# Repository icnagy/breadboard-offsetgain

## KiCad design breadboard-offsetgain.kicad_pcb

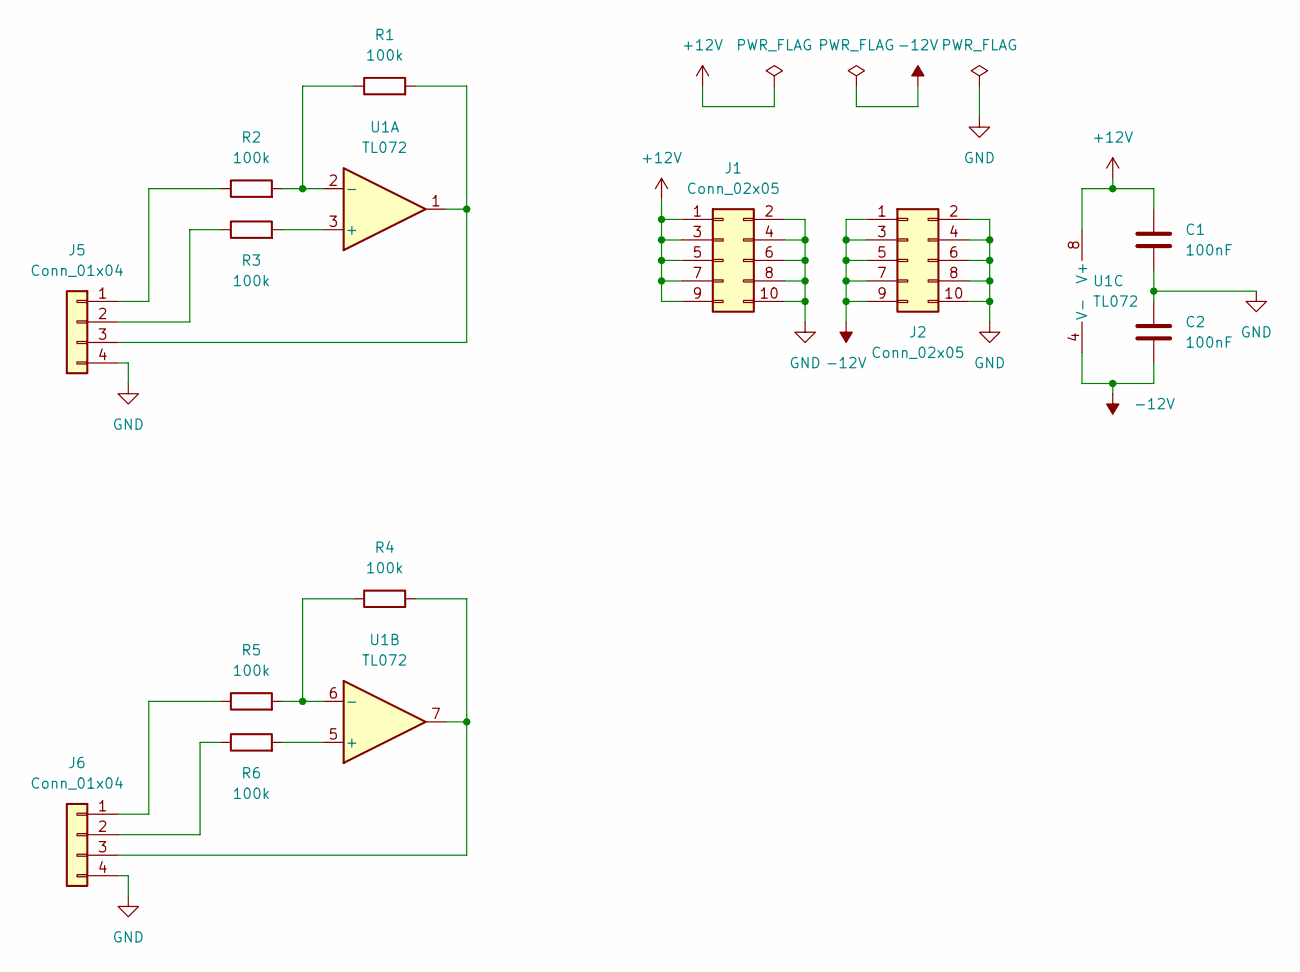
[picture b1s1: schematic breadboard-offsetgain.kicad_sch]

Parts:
C1, C2: 100nF; C_Disc_D4.7mm_W2.5mm_P5.00mm
J1, J2: Conn_02x05; PinHeader_2x05_P2.54mm_Vertical
J5, J6: Conn_01x04; PinHeader_1x04_P2.54mm_Vertical
R1, R2, R3, R4, R5, R6: 100k; R_Axial_DIN0207_L6.3mm_D2.5mm_P2.54mm_Vertical
U1: TL072; DIP-8_W7.62mm_Socket

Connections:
+12V: C1.1, J1.1, J1.3, J1.5, J1.7, J1.9, U1.8 (V+)
-12V: C2.2, J2.1, J2.3, J2.5, J2.7, J2.9, U1.4 (V-)
GND: C1.2, C2.1, J1.2, J1.4, J1.6, J1.8, J1.10, J2.2, J2.4, J2.6, J2.8, J2.10, J5.4, J6.4
unnamed: J5.1, R2.1
unnamed: J5.2, R3.1
unnamed: J5.3, R1.2, U1.1
unnamed: J6.1, R5.1
unnamed: J6.2, R6.1
unnamed: J6.3, R4.2, U1.7
unnamed: R1.1, R2.2, U1.2 (-)
unnamed: R3.2, U1.3 (+)
unnamed: R4.1, R5.2, U1.6 (-)
unnamed: R6.2, U1.5 (+)

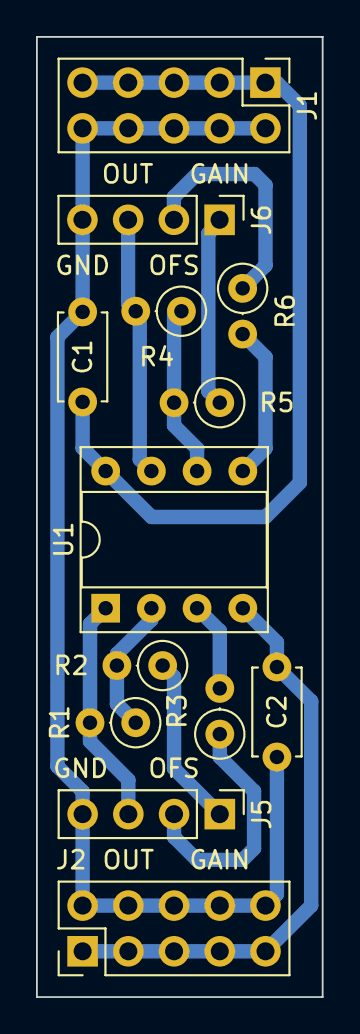
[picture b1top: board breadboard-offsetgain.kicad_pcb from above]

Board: 2 copper layers, 15.9 x 53.3 mm, 13 parts (0 on the bottom side), 13 nets.

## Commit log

2022-06-10 Add image and schematic
2022-06-10 Add readme
2023-05-29 Kicad 7.0.5 upgrade
